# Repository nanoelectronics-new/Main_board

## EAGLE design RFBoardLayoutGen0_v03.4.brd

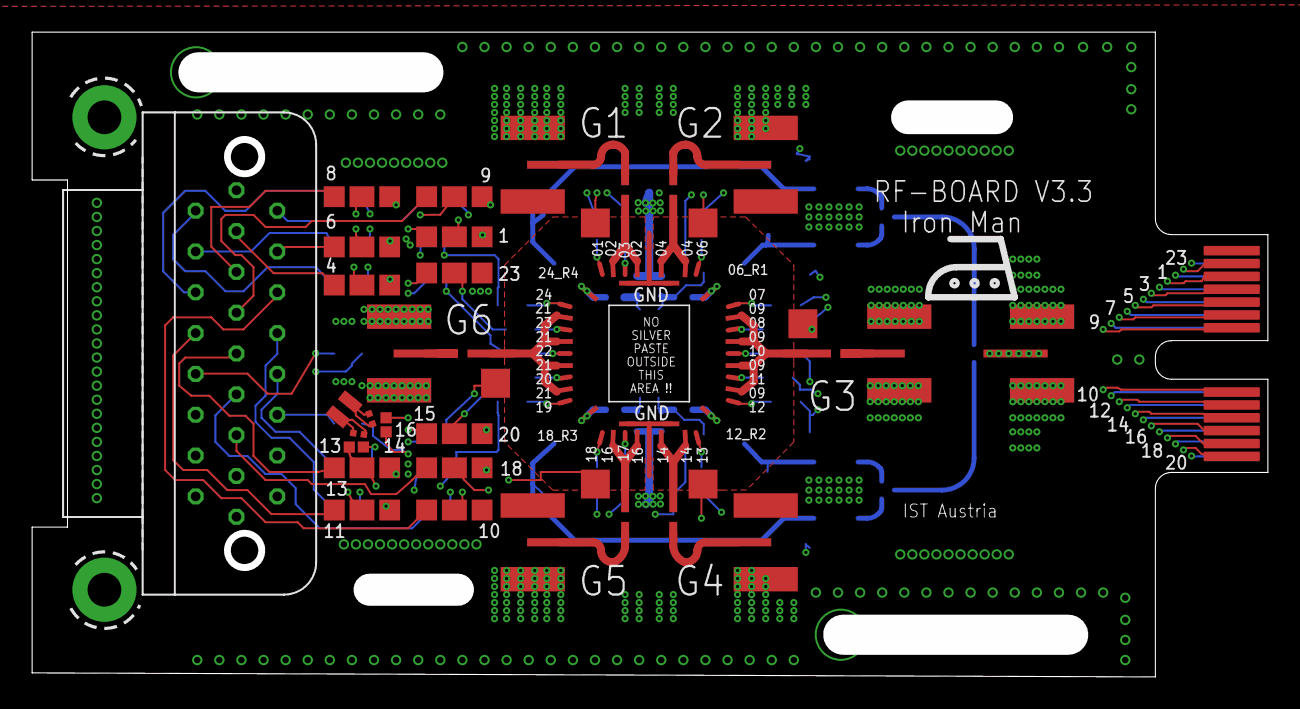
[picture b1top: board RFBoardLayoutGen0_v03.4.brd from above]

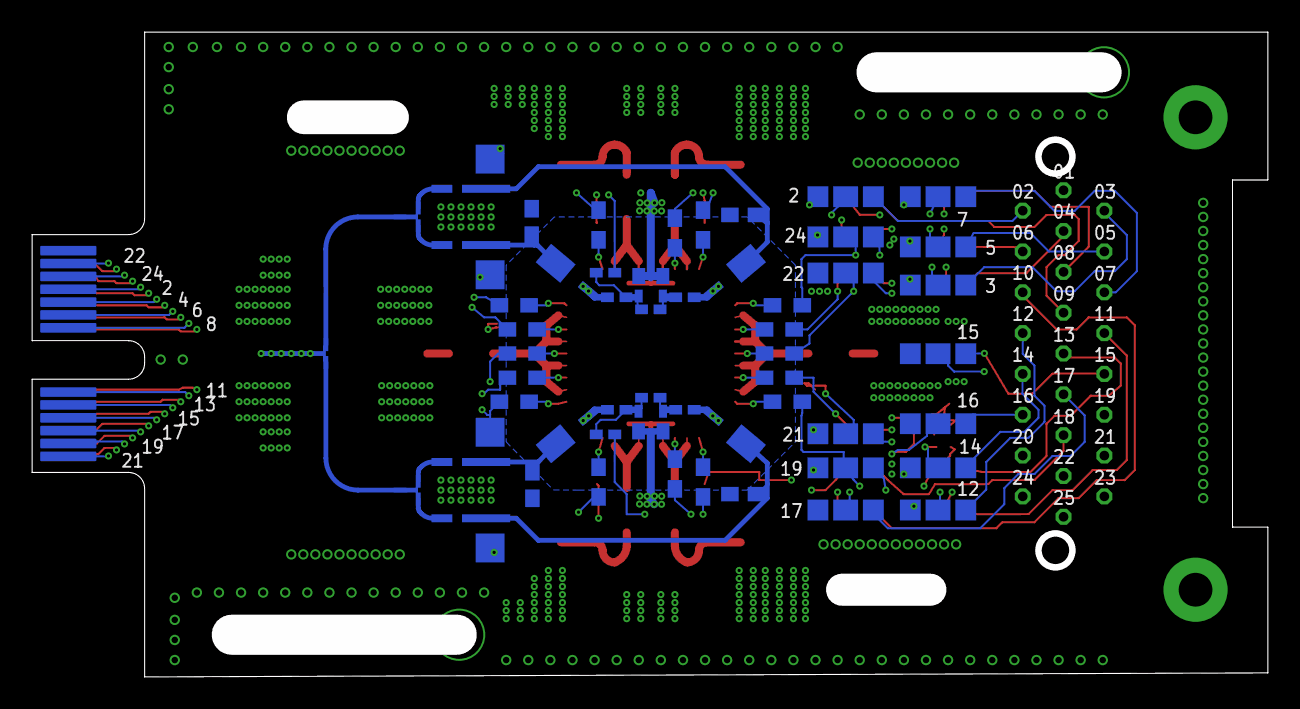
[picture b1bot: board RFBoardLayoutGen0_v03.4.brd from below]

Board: 6 copper layers, 76.9 x 40.1 mm, 88 parts (9 on the bottom side), 96 nets.

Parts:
B$1, B$3, B$4, B$6, B$8, B$10: BIASTEEDOWN; BIAS_TEE_DOWN_0603
B$2, B$5, B$7, B$9: BIASTEEUP; BIAS_TEE_UP_0603
E$2: 25_SOCKET_M83513/13-D_V2
L$1, L$2, L$3, L$4: L_MATCH
LP$1, LP$2, LP$3, LP$4, LP$5, LP$6, LP$15, LP$16, LP$17, LP$18, LP$19, LP$20: LP-FILTER/1-STAGETOP; LP-FILTER/1_STAGE/OS/0603_TOP
LP$7, LP$8, LP$9, LP$10, LP$11, LP$12, LP$13, LP$14, LP$21, LP$22, LP$23, LP$24: LP-FILTER/1-STAGEBOT; LP-FILTER/1_STAGE/OS/0603_BOTTOM
R$1, R$3, R$6, R$7, R$9, R$10, R$11, R$12, R$19, R$20, R$22, R$23, R$24, R$25, R$29, R$30: 10K; LP-FILTER/RESISTOR/0603_BOTTOM
S$1, S$2, S$3, S$4, S$5, S$6, S$7: MC-921WIDE; SMP_STRAIGHT_MINI_WIDE
TP1, TP2, TP3, TP4: TPTP07SQ; TP07SQ
U$1: MEC8-113-02-L-D-RA1MBRD; MEC8-113-02-L-D-RA1
U$2: TEMPSENS; RX-BR_V1
U$3, U$4, U$5: TJUNCTION; T_JUNCTION_0.3MM
U$6: 24DC+10RF_V2.0; 24DC+10RF/400MU-PADS/0.7X0.7_V2.0
U$7, U$8, U$9, U$10: LP-FILTER/CAPACITOR/0603; LP-FILTER/CAPACITOR/0603_BOTTOM
U$11, U$12, U$13, U$14: LP-FILTER/VARACTOR/0402
U$15, U$16, U$17, U$18: LP-FILTER/CAPACITOR/0402
U$19, U$20, U$21, U$22: LP-FILTER/RESISTOR/0402; LP-FILTER/CAPACITOR/0402

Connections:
C$1: E$2.01, LP$16.$1
C$2: E$2.02, LP$10.$1
C$3: E$2.03, LP$9.$1
C$4: E$2.04, LP$3.$1
C$5: E$2.05, LP$8.$1
C$6: E$2.06, LP$2.$1
C$7: E$2.07, LP$7.$1
C$8: E$2.08, LP$1.$1
C$9: E$2.09, LP$15.$1
C$10: E$2.10, LP$20.$1
C$11: E$2.11, LP$6.$1
C$12: E$2.12, LP$14.$1
C$13: E$2.13, LP$5.$1
C$14: E$2.14, LP$13.$1
C$15: E$2.15, LP$4.$1
C$16: E$2.16, LP$12.$1
C$17: E$2.17, LP$11.$1
C$18: E$2.18, LP$19.$1
C$19: E$2.19, LP$24.$1
C$20: E$2.20, LP$18.$1
C$21: E$2.21, LP$23.$1
C$22: E$2.22, LP$22.$1
C$23: E$2.23, LP$17.$1
C$24: E$2.24, LP$21.$1
D$1: LP$16.$4, R$1.IN, U$1.21
D$2: B$1.LF, LP$10.$4, U$1.20
D$3: LP$9.$4, R$3.IN, U$1.19
D$4: B$2.LF, LP$3.$4, U$1.18
D$5: LP$8.$4, U$1.17, U$22.IN
D$6: B$8.LF, LP$2.$4, R$6.IN, U$1.16
D$7: LP$7.$4, R$25.IN, U$1.15
D$8: LP$1.$4, R$7.IN, U$1.14
D$9: B$3.LF, LP$15.$4, U$1.13
D$10: LP$20.$4, R$9.IN, U$1.11
D$11: LP$6.$4, R$10.IN, U$1.12
D$12: B$9.LF, LP$14.$4, R$11.IN, U$1.9
D$13: LP$5.$4, R$12.IN, TP4.TP, U$1.10
D$14: B$4.LF, LP$13.$4, TP3.TP, U$1.7
D$15: LP$4.$4, TP1.TP, U$1.8, U$21.OUT
D$16: B$5.LF, LP$12.$4, TP2.TP, U$1.5
D$17: LP$11.$4, R$29.IN, U$1.6
D$18: B$10.LF, LP$19.$4, R$30.IN, U$1.3
D$19: LP$24.$4, R$19.IN, U$1.4
D$20: LP$18.$4, R$20.IN, U$1.1
D$21: B$6.LF, LP$23.$4, U$1.2
D$22: LP$22.$4, R$22.IN, U$1.24
D$23: LP$17.$4, R$23.IN, U$1.23
D$24: B$7.LF, LP$21.$4, R$24.IN, U$1.22
DC$1: R$1.OUT, U$6.DC$01
DC$3: R$3.OUT, U$6.DC§03
DC$5: B$2.OUT, U$6.RF$04_G21, U$6.RF$04_G22
DC$6: R$6.OUT, U$6.DC§06
DC$10: B$3.OUT, U$6.RF$09_G31, U$6.RF$09_G32, U$6.RF$09_G33, U$6.RF$09_G34
DC$13: R$12.OUT, U$6.DC$13
DC$19: R$19.OUT, U$6.DC§19
DC$20: R$20.OUT, U$6.DC§20
DC$24: R$24.OUT, U$6.DC§24
GND: E$2.25, LP$1.$6, LP$2.$6, LP$3.$6, LP$4.$6, LP$5.$6, LP$6.$6, LP$7.$6, LP$8.$6, LP$9.$6, LP$10.$6, LP$11.$6, LP$12.$6, LP$13.$6, LP$14.$6, LP$15.$6, LP$16.$6, LP$17.$6, LP$18.$6, LP$19.$6, LP$20.$6, LP$21.$6, LP$22.$6, LP$23.$6, LP$24.$6, S$1.2@1, S$1.2@2, S$2.2@1, S$2.2@2, S$3.2@1, S$3.2@2, S$4.2@1, S$4.2@2, S$5.2@1, S$5.2@2, S$6.2@1, S$6.2@2, S$7.2@1, S$7.2@2, U$1.25, U$1.26, U$6.GND$1, U$6.GND$2, U$6.GND$3, U$6.GND$4, U$6.GND$5, U$6.GND$6, U$7.OUT, U$8.OUT, U$9.OUT, U$10.OUT, U$11.OUT, U$12.OUT, U$13.OUT, U$14.OUT
unnamed: B$6.HF, S$1.1
unnamed: L$3.OUT, U$6.RF$12_R2, U$18.IN
unnamed: B$1.OUT, U$6.RF$02_G11, U$6.RF$02_G12
unnamed: R$25.OUT, U$6.DC§07
unnamed: B$1.HF, S$7.1
unnamed: B$2.HF, S$6.1
unnamed: B$4.OUT, U$6.RF$14_G41, U$6.RF$14_G42
unnamed: B$5.OUT, U$6.RF$16_G51, U$6.RF$16_G52
unnamed: L$4.OUT, U$6.RF$18_R3, U$16.IN
unnamed: L$1.OUT, U$6.RF$24_R4, U$15.OUT
unnamed: L$2.OUT, U$6.RF$06_R1, U$17.OUT
unnamed: R$7.OUT, U$6.DC§08
unnamed: B$9.OUT, L$3.IN, U$9.IN
unnamed: B$8.OUT, L$2.IN, U$10.IN
unnamed: B$9.HF, U$5.P$3
unnamed: B$5.HF, S$2.1
unnamed: B$4.HF, S$3.1
unnamed: B$3.HF, S$4.1
unnamed: B$7.HF, U$3.P$3
unnamed: B$6.OUT, U$6.RF$21_G61, U$6.RF$21_G62, U$6.RF$21_G63, U$6.RF$21_G64
unnamed: S$5.1, U$4.P$1
unnamed: B$10.HF, U$5.P$2
unnamed: B$8.HF, U$3.P$2
unnamed: R$9.OUT, U$6.DC§10
unnamed: U$3.P$1, U$4.P$3
unnamed: U$4.P$2, U$5.P$1
unnamed: R$10.OUT, U$6.DC§11
unnamed: R$11.OUT, U$6.DC§12
unnamed: U$13.IN, U$17.IN, U$19.OUT, U$22.OUT
unnamed: R$29.OUT, U$6.DC§17
unnamed: R$30.OUT, U$6.DC§18
unnamed: R$22.OUT, U$6.DC§22
unnamed: R$23.OUT, U$6.DC§23
unnamed: U$12.IN, U$18.OUT, U$20.OUT, U$21.IN
unnamed: U$14.IN, U$15.IN, U$19.IN
unnamed: U$11.IN, U$16.OUT, U$20.IN
RF$3: B$10.OUT, L$4.IN, U$8.IN
RF$4: B$7.OUT, L$1.IN, U$7.IN

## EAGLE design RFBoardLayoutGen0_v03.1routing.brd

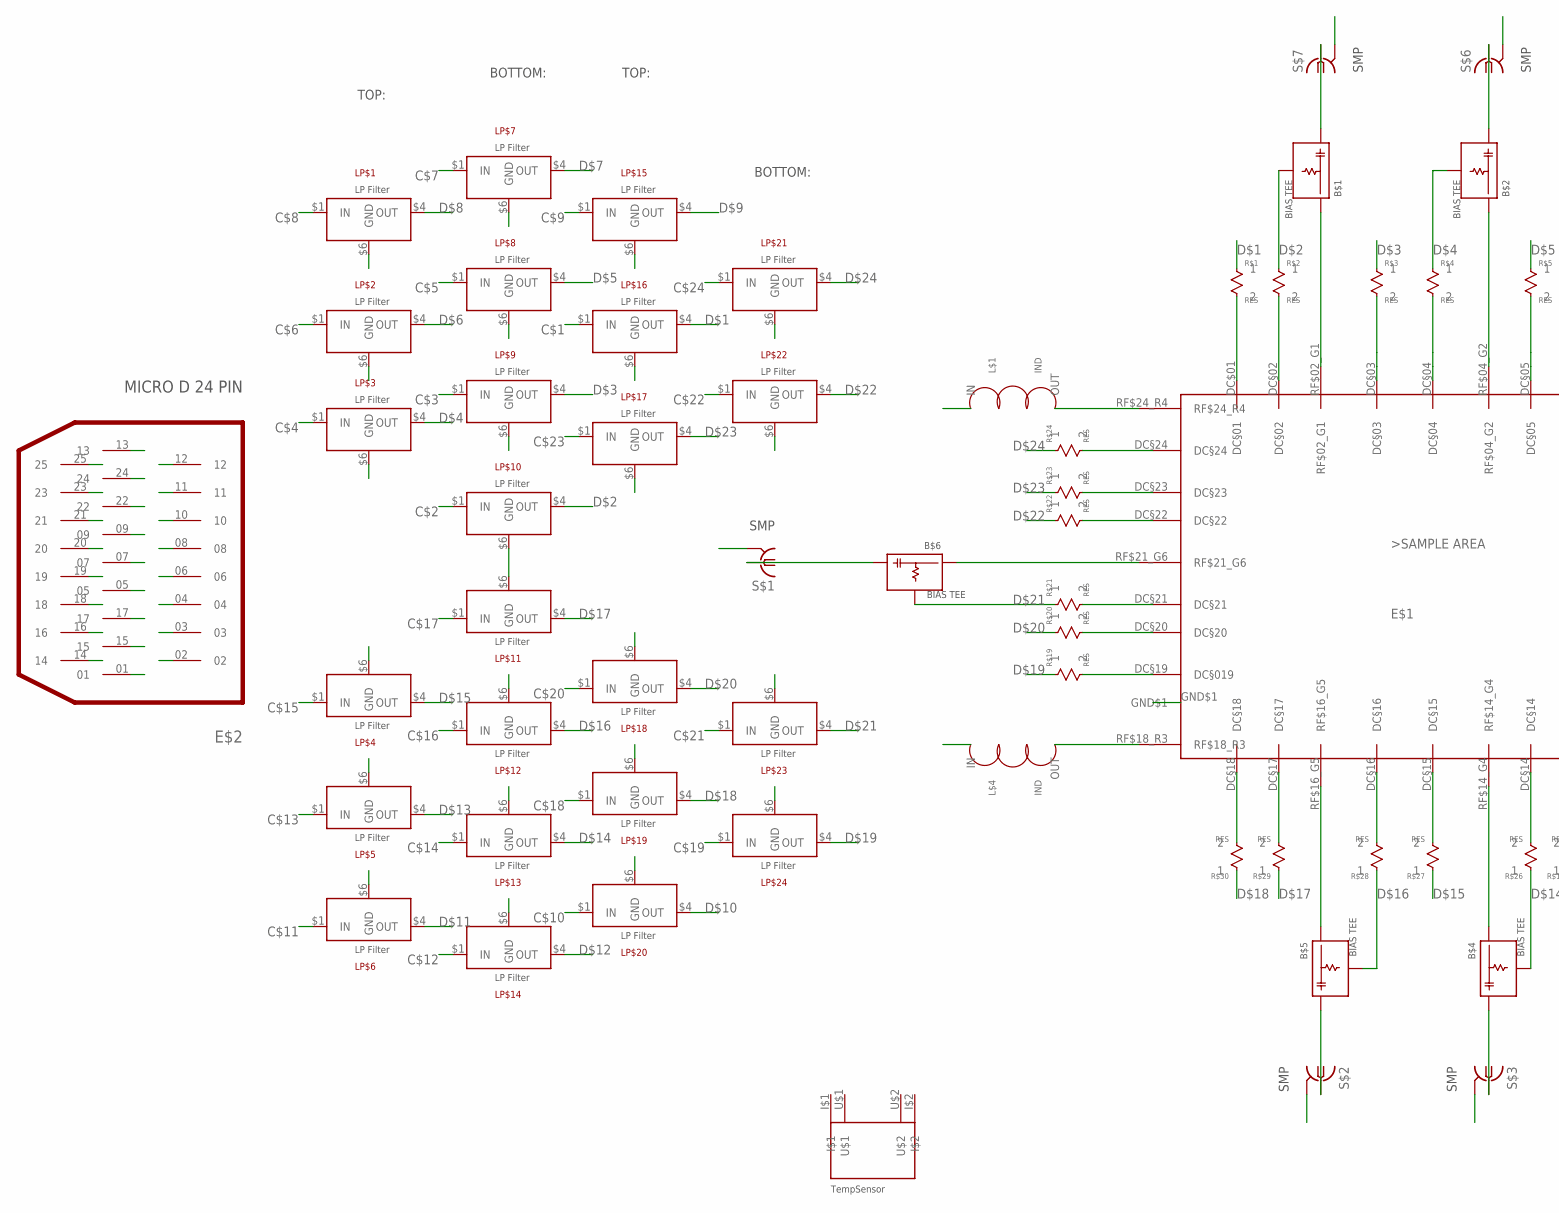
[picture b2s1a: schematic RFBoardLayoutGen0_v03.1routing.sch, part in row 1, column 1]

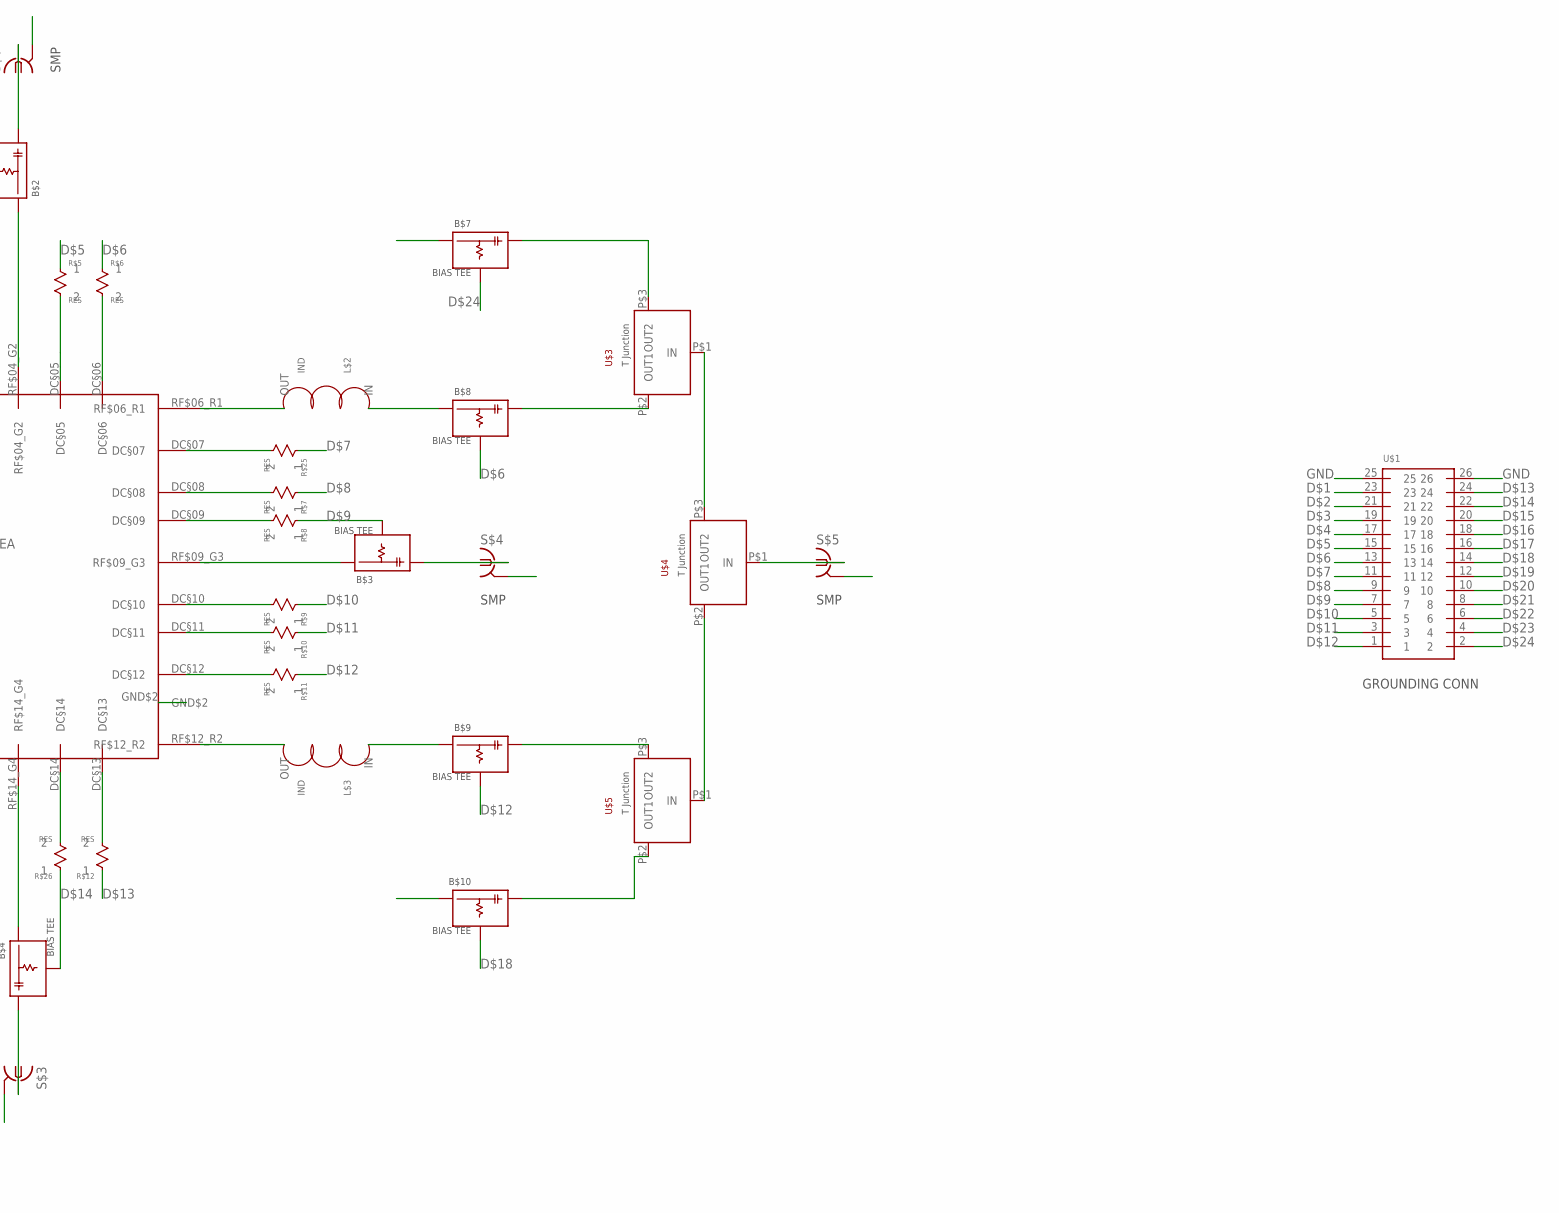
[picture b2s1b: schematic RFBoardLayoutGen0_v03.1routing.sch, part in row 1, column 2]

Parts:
B$1, B$3, B$4, B$6, B$8, B$10: BIASTEEDOWN; BIAS_TEE_DOWN_0603
B$2, B$5, B$7, B$9: BIASTEEUP; BIAS_TEE_UP_0603
E$1: 24DC+10RF; 24DC+10RF/400MU-PADS/0.7X0.7_V1.0
E$2: 25_SOCKET_M83513(13-DPINOUT2; 25_SOCKET_M83513/13-D_V2
L$1, L$2, L$3, L$4: L_MATCH
LP$1, LP$2, LP$3, LP$4, LP$5, LP$6, LP$15, LP$16, LP$17, LP$18, LP$19, LP$20: LP-FILTER/1-STAGETOP; LP-FILTER/1_STAGE/OS/0603_TOP
LP$7, LP$8, LP$9, LP$10, LP$11, LP$12, LP$13, LP$14, LP$21, LP$22, LP$23, LP$24: LP-FILTER/1-STAGEBOT; LP-FILTER/1_STAGE/OS/0603_BOTTOM
R$1, R$2, R$3, R$4, R$5, R$6, R$7, R$8, R$9, R$10, R$11, R$12, R$19, R$20, R$21, R$22, R$23, R$24, R$25, R$26, R$27, R$28, R$29, R$30: 10K; LP-FILTER/RESISTOR/0603_BOTTOM
S$1, S$2, S$3, S$4, S$5, S$6, S$7: MC-921; SMP_STRAIGHT_MINI
U$1: MEC8-113-02-L-D-RA1MBRD; MEC8-113-02-L-D-RA1
U$2: TEMPSENS; RX-BR_V1
U$3, U$4, U$5: TJUNCTION; T_JUNCTION_0.3MM

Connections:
C$1: E$2.01, LP$16.$1 (IN)
C$2: E$2.02, LP$10.$1 (IN)
C$3: E$2.03, LP$9.$1 (IN)
C$4: E$2.04, LP$3.$1 (IN)
C$5: E$2.05, LP$8.$1 (IN)
C$6: E$2.06, LP$2.$1 (IN)
C$7: E$2.07, LP$7.$1 (IN)
C$8: E$2.08, LP$1.$1 (IN)
C$9: E$2.09, LP$15.$1 (IN)
C$10: E$2.10, LP$20.$1 (IN)
C$11: E$2.11, LP$6.$1 (IN)
C$12: E$2.12, LP$14.$1 (IN)
C$13: E$2.13, LP$5.$1 (IN)
C$14: E$2.14, LP$13.$1 (IN)
C$15: E$2.15, LP$4.$1 (IN)
C$16: E$2.16, LP$12.$1 (IN)
C$17: E$2.17, LP$11.$1 (IN)
C$18: E$2.18, LP$19.$1 (IN)
C$19: E$2.19, LP$24.$1 (IN)
C$20: E$2.20, LP$18.$1 (IN)
C$21: E$2.21, LP$23.$1 (IN)
C$22: E$2.22, LP$22.$1 (IN)
C$23: E$2.23, LP$17.$1 (IN)
C$24: E$2.24, LP$21.$1 (IN)
D$1: LP$16.$4 (OUT), R$1.IN (1), U$1.23
D$2: B$1.LF, LP$10.$4 (OUT), R$2.IN (1), U$1.21
D$3: LP$9.$4 (OUT), R$3.IN (1), U$1.19
D$4: B$2.LF, LP$3.$4 (OUT), R$4.IN (1), U$1.17
D$5: LP$8.$4 (OUT), R$5.IN (1), U$1.15
D$6: B$8.LF, LP$2.$4 (OUT), R$6.IN (1), U$1.13
D$7: LP$7.$4 (OUT), R$25.IN (1), U$1.11
D$8: LP$1.$4 (OUT), R$7.IN (1), U$1.9
D$9: B$3.LF, LP$15.$4 (OUT), R$8.IN (1), U$1.7
D$10: LP$20.$4 (OUT), R$9.IN (1), U$1.5
D$11: LP$6.$4 (OUT), R$10.IN (1), U$1.3
D$12: B$9.LF, LP$14.$4 (OUT), R$11.IN (1), U$1.1
D$13: LP$5.$4 (OUT), R$12.IN (1), U$1.24
D$14: B$4.LF, LP$13.$4 (OUT), R$26.IN (1), U$1.22
D$15: LP$4.$4 (OUT), R$27.IN (1), U$1.20
D$16: B$5.LF, LP$12.$4 (OUT), R$28.IN (1), U$1.18
D$17: LP$11.$4 (OUT), R$29.IN (1), U$1.16
D$18: B$10.LF, LP$19.$4 (OUT), R$30.IN (1), U$1.14
D$19: LP$24.$4 (OUT), R$19.IN (1), U$1.12
D$20: LP$18.$4 (OUT), R$20.IN (1), U$1.10
D$21: B$6.LF, LP$23.$4 (OUT), R$21.IN (1), U$1.8
D$22: LP$22.$4 (OUT), R$22.IN (1), U$1.6
D$23: LP$17.$4 (OUT), R$23.IN (1), U$1.4
D$24: B$7.LF, LP$21.$4 (OUT), R$24.IN (1), U$1.2
DC$1: E$1.DC$01 (DC§01), R$1.OUT (2)
DC$2: E$1.DC§02, R$2.OUT (2)
DC$3: E$1.DC§03, R$3.OUT (2)
DC$4: E$1.DC§04, R$4.OUT (2)
DC$5: E$1.DC§05, R$5.OUT (2)
DC$6: E$1.DC§06, R$6.OUT (2)
DC$7: E$1.DC§07, R$25.OUT (2)
DC$8: E$1.DC§08, R$7.OUT (2)
DC$9: E$1.DC§09, R$8.OUT (2)
DC$10: E$1.DC§10, R$9.OUT (2)
DC$11: E$1.DC§11, R$10.OUT (2)
DC$12: E$1.DC§12, R$11.OUT (2)
DC$13: E$1.DC§13, R$12.OUT (2)
DC$14: E$1.DC§14, R$26.OUT (2)
DC$15: E$1.DC§15, R$27.OUT (2)
DC$16: E$1.DC§16, R$28.OUT (2)
DC$17: E$1.DC§17, R$29.OUT (2)
DC$18: E$1.DC§18, R$30.OUT (2)
DC$19: E$1.DC§19 (DC§019), R$19.OUT (2)
DC$20: E$1.DC§20, R$20.OUT (2)
DC$21: E$1.DC§21, R$21.OUT (2)
DC$22: E$1.DC§22, R$22.OUT (2)
DC$23: E$1.DC§23, R$23.OUT (2)
DC$24: E$1.DC§24, R$24.OUT (2)
GND: E$1.GND$1, E$1.GND$2, E$2.25, LP$1.$6 (GND), LP$2.$6 (GND), LP$3.$6 (GND), LP$4.$6 (GND), LP$5.$6 (GND), LP$6.$6 (GND), LP$7.$6 (GND), LP$8.$6 (GND), LP$9.$6 (GND), LP$10.$6 (GND), LP$11.$6 (GND), LP$12.$6 (GND), LP$13.$6 (GND), LP$14.$6 (GND), LP$15.$6 (GND), LP$16.$6 (GND), LP$17.$6 (GND), LP$18.$6 (GND), LP$19.$6 (GND), LP$20.$6 (GND), LP$21.$6 (GND), LP$22.$6 (GND), LP$23.$6 (GND), LP$24.$6 (GND), S$1.2@1 (GND), S$1.2@2 (GND), S$2.2@1 (GND), S$2.2@2 (GND), S$3.2@1 (GND), S$3.2@2 (GND), S$4.2@1 (GND), S$4.2@2 (GND), S$5.2@1 (GND), S$5.2@2 (GND), S$6.2@1 (GND), S$6.2@2 (GND), S$7.2@1 (GND), S$7.2@2 (GND), U$1.25, U$1.26
unnamed: B$6.HF, S$1.1
unnamed: E$1.RF$12_R2, L$3.OUT
unnamed: B$1.OUT, E$1.RF$02_G1
unnamed: B$2.OUT, E$1.RF$04_G2
unnamed: B$1.HF, S$7.1
unnamed: B$2.HF, S$6.1
unnamed: B$5.OUT, E$1.RF$16_G5
unnamed: B$4.OUT, E$1.RF$14_G4
unnamed: E$1.RF$18_R3, L$4.OUT
unnamed: E$1.RF$24_R4, L$1.OUT
unnamed: E$1.RF$06_R1, L$2.OUT
unnamed: B$3.OUT, E$1.RF$09_G3
unnamed: B$9.OUT, L$3.IN
unnamed: B$8.OUT, L$2.IN
unnamed: B$9.HF, U$5.P$3 (OUT2)
unnamed: B$5.HF, S$2.1
unnamed: B$4.HF, S$3.1
unnamed: B$3.HF, S$4.1
unnamed: B$7.HF, U$3.P$3 (OUT2)
unnamed: B$6.OUT, E$1.RF$21_G6
unnamed: S$5.1, U$4.P$1 (IN)
unnamed: B$10.HF, U$5.P$2 (OUT1)
unnamed: B$8.HF, U$3.P$2 (OUT1)
unnamed: U$3.P$1 (IN), U$4.P$3 (OUT2)
unnamed: U$4.P$2 (OUT1), U$5.P$1 (IN)
RF$3: B$10.OUT, L$4.IN
RF$4: B$7.OUT, L$1.IN

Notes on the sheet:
TOP:
BOTTOM:

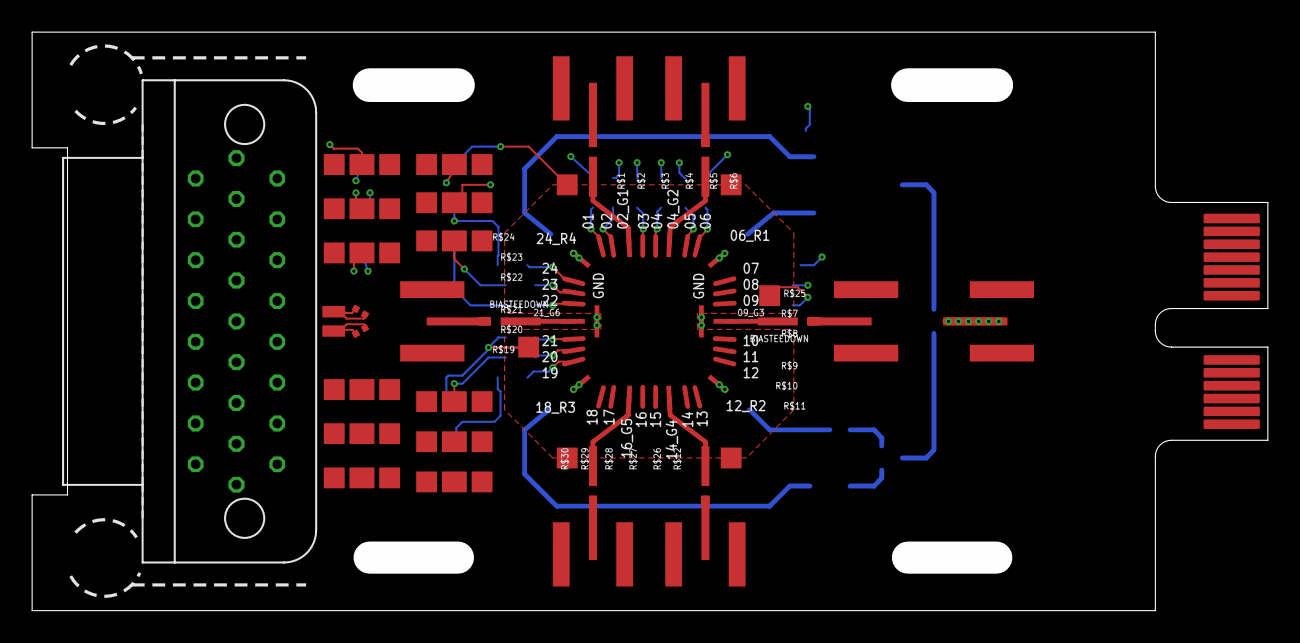
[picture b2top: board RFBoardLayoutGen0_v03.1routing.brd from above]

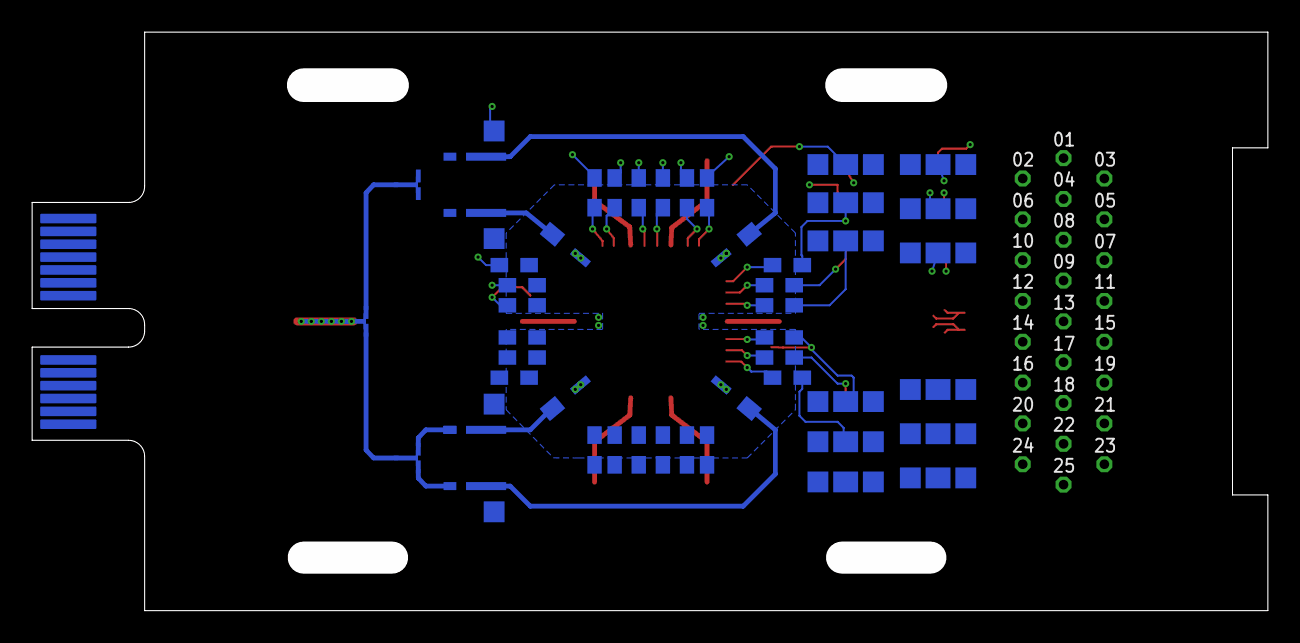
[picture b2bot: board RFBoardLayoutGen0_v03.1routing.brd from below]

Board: 6 copper layers, 76.9 x 36.0 mm, 77 parts (9 on the bottom side), 100 nets.

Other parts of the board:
E$30: SMD0.8-0,5

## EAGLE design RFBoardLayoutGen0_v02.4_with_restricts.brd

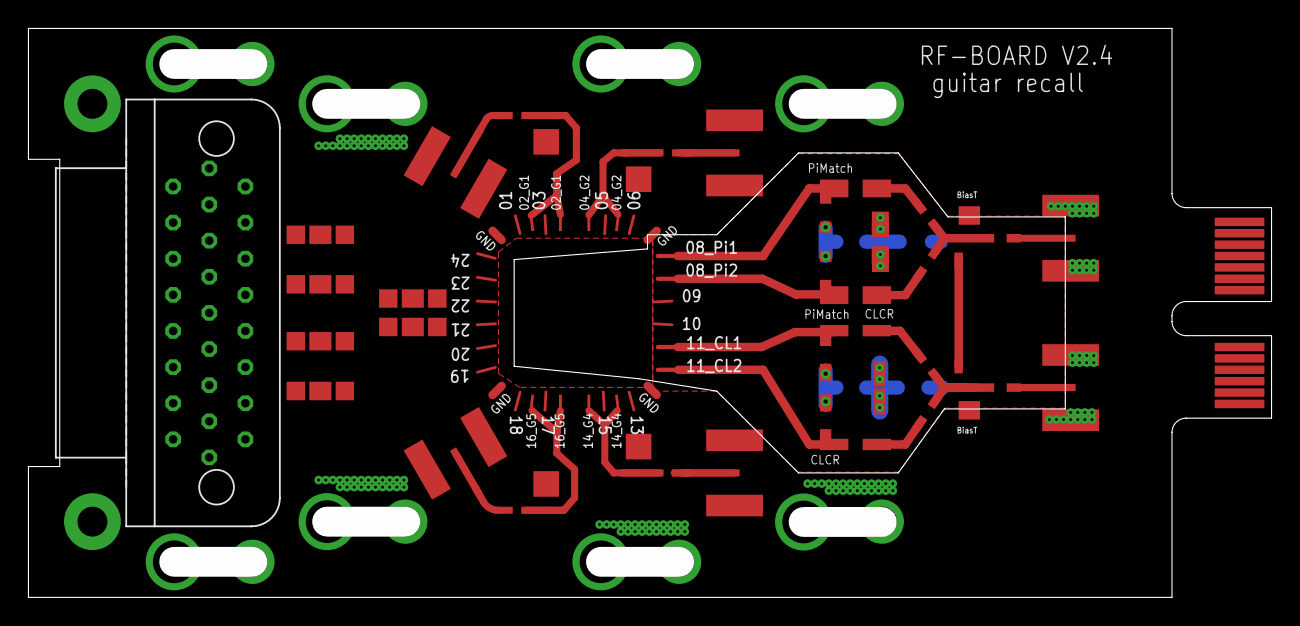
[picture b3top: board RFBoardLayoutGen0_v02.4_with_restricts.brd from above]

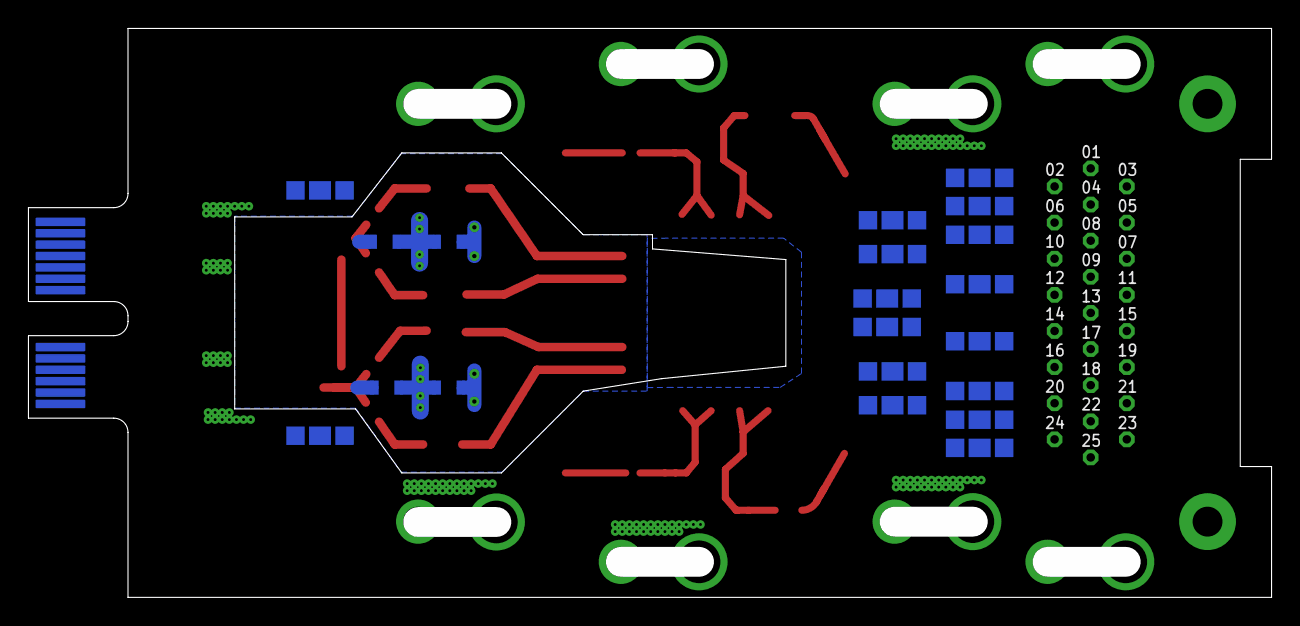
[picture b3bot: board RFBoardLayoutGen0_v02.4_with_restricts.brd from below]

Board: 4 copper layers, 87.4 x 40.0 mm, 61 parts (14 on the bottom side), 45 nets.

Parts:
B$1, B$4: BIAS_TEE_DOWN_0603
B$2, B$5: BIAS_TEE_UP_0603
E$1: 24DC+4RF/400MU-PADS/10.0X10.0_V1.5
E$2: 25_SOCKET_M83513/13-D
E$3: MEC8-113-02-L-D-RA1
E$4, E$5, E$6, E$7, E$8, E$11, E$12, E$13, E$14, E$15: LP-FILTER/1_STAGE/OS/0603_TOP_V1_01
E$9: PI_MATCH_V01_UP
E$10: CLCR_V01_DOWN
E$16, E$17, E$18, E$19, E$20, E$21, E$22, E$23, E$24, E$25, E$27, E$28: LP-FILTER/1_STAGE/OS/0603_BOTTOM_V1_01
E$26, E$33: SMP_STRAIGHT_MINI_WIDE_V1_01
E$29: BIAS_TEE_UP_V01
E$30: BIAS_TEE_DOWN_V01
E$31, E$34, E$35, E$36, E$38, E$39, E$40, E$41, E$42, E$43, E$44, E$45, E$46, E$47, E$48, E$49, E$50, E$51, E$52, E$54: SMD1-0,6
E$32: PI_MATCH_V01_DOWN
E$37: CLCR_V01_UP
S$2, S$3, S$6, S$7: MC-921SMALL; SMP_STRAIGHT_MINI_WIDE

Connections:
D$2: B$1.LF, E$3.19, E$6.$2
D$4: B$2.LF, E$3.21, E$4.$2
GND: E$1.P$1, E$1.P$3, E$1.P$6, E$2.13, E$3.14, E$4.GND@1, E$5.GND@1, E$6.GND@1, E$7.GND@1, E$8.GND@1, E$11.GND@1, E$12.GND@1, E$13.GND@1, E$14.GND@1, E$15.GND@1, E$16.GND@1, E$17.GND@1, E$18.GND@1, E$19.GND@1, E$20.GND@1, E$21.GND@1, E$22.GND@1, E$23.GND@1, E$24.GND@1, E$25.GND@1, E$26.GND, E$26.GND@1, E$27.GND@1, E$28.GND@1, E$33.GND, E$33.GND@1, S$2.2@1, S$2.2@2, S$3.2@1, S$3.2@2, S$6.2@1, S$6.2@2, S$7.2@1, S$7.2@2
S$1: E$1.P$30, E$22.$2
S$2: E$1.P$44, E$3.8, E$21.$2, E$47.1
S$55: E$1.P$49, E$3.2, E$27.$2, E$46.1
S$67: E$2.24, E$11.$1
S$68: E$1.P$29, E$3.9, E$15.$2
S$76: E$2.11, E$15.$1
S$79: E$1.P$27, E$3.16, E$19.$2
S$80: E$2.12, E$19.$1
S$83: E$2.23, E$22.$1
S$84: E$1.P$26, E$3.17, E$8.$2
S$85: E$2.25, E$8.$1
S$86: E$1.P$38, E$3.18, E$16.$2, E$36.1
S$88: E$2.01, E$16.$1
S$89: E$1.P$31, E$3.7, E$7.$2
S$90: E$2.10, E$7.$1
S$95: E$2.22, E$21.$1
S$144: E$2.14, E$6.$1
S$145: E$1.P$40, E$3.20, E$23.$2
S$146: E$2.02, E$23.$1
S$147: B$5.LF, E$3.6, E$17.$2
S$149: E$2.15, E$4.$1
S$150: E$1.P$42, E$3.24, E$20.$2
S$151: E$2.03, E$20.$1
S$152: E$1.P$45, E$3.5, E$12.$2
S$154: E$2.09, E$12.$1
S$155: B$4.LF, E$3.4, E$18.$2
S$156: E$2.21, E$17.$1
S$157: E$1.P$4, E$3.3, E$5.$2
S$158: E$2.08, E$5.$1
S$160: E$2.20, E$18.$1
S$162: E$2.16, E$24.$1
S$168: E$2.17, E$14.$1
S$169: E$1.P$34, E$3.26, E$25.$2
S$170: E$2.05, E$25.$1
S$171: E$2.07, E$27.$1
S$174: E$1.P$28, E$3.15, E$11.$2
S$175: E$2.06, E$13.$1
S$177: E$1.P$35, E$3.11, E$28.$2
S$178: E$2.18, E$28.$1
S$183: E$3.12, E$13.$2, E$29.P$1
S$190: E$3.23, E$14.$2, E$30.P$1
S$211: E$1.P$43, E$3.22, E$24.$2, E$34.1

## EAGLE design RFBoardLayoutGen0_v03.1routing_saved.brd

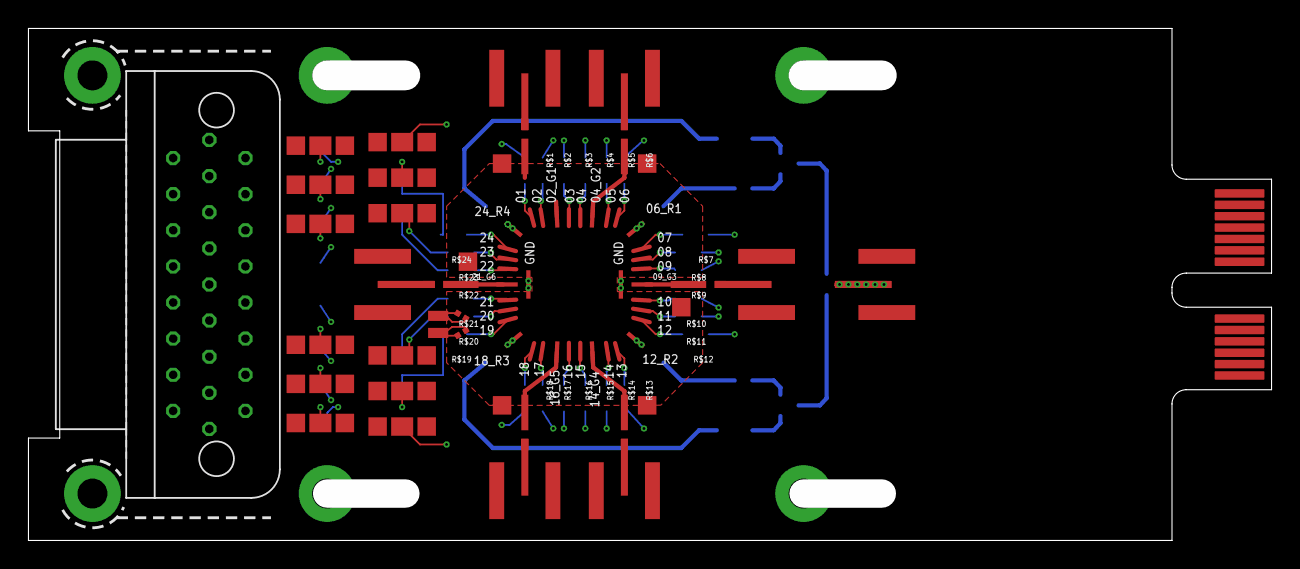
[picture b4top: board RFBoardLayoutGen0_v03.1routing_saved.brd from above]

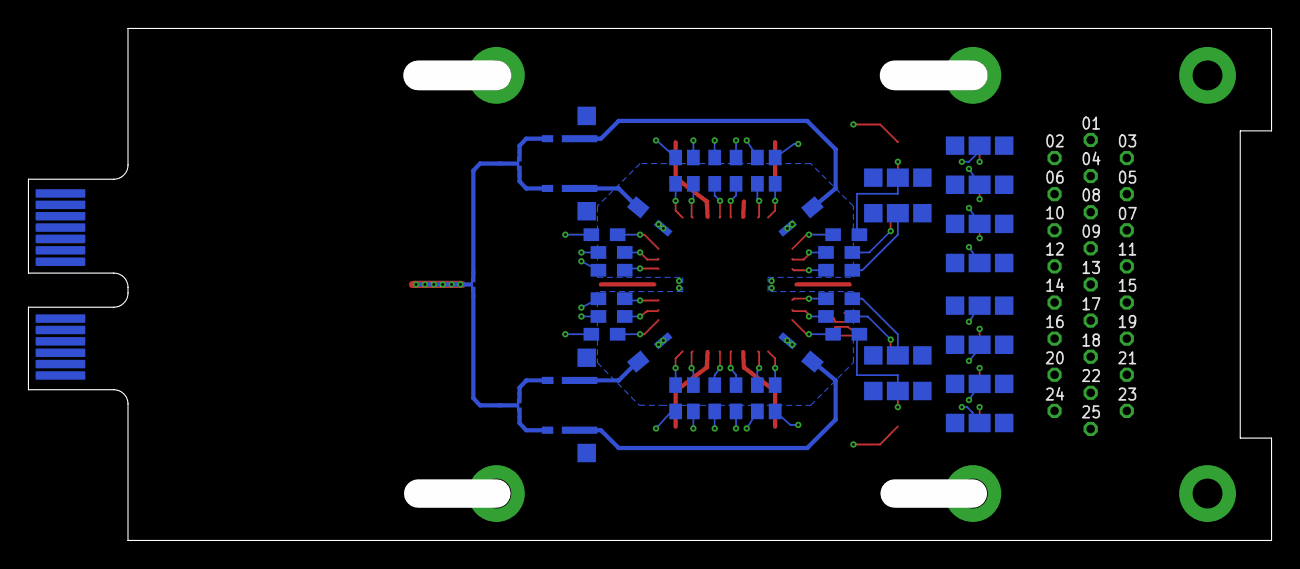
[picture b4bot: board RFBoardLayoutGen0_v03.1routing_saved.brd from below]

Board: 6 copper layers, 87.4 x 36.0 mm, 77 parts (9 on the bottom side), 48 nets.

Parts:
B$1, B$4, B$8, B$10: BIAS_TEE_DOWN_0603
B$2, B$3, B$5, B$6, B$7, B$9: BIAS_TEE_UP_0603
E$1: 24DC+10RF/400MU-PADS/0.7X0.7_V1.0
E$2: 25_SOCKET_M83513/13-D
E$3: MEC8-113-02-L-D-RA1
E$30: SMD0.8-0,5
E$40: RX-BR_V1
E$48, E$50, E$51: T_JUNCTION_0.3MM
L$1, L$2, L$3, L$4: L_MATCH
LP$1, LP$2, LP$3, LP$4, LP$5, LP$6, LP$15, LP$16, LP$17, LP$18, LP$19, LP$20: LP-FILTER/1_STAGE/OS/0603_TOP
LP$7, LP$8, LP$9, LP$10, LP$11, LP$12, LP$13, LP$14, LP$21, LP$22, LP$23, LP$24: LP-FILTER/1_STAGE/OS/0603_BOTTOM
R$1, R$2, R$3, R$4, R$5, R$6, R$7, R$8, R$9, R$10, R$11, R$12, R$13, R$14, R$15, R$16, R$17, R$18, R$19, R$20, R$21, R$22, R$23, R$24: 10K; LP-FILTER/RESISTOR/0603_BOTTOM
S$1, S$2, S$3, S$4, S$5, S$6, S$7: SMP_STRAIGHT_MINI

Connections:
S$166: E$1.DC§24, R$24.IN
S$180: E$1.DC§23, R$23.IN
S$181: E$1.DC§22, R$22.IN
S$184: E$1.DC§21, R$21.IN
S$185: E$1.DC§20, R$20.IN
S$186: E$1.DC§19, R$19.IN
S$187: E$1.DC$01, R$1.OUT
S$188: E$1.DC§02, R$2.OUT
S$189: E$1.DC§03, R$3.OUT
S$191: E$1.DC§04, R$4.OUT
S$193: E$1.DC§05, R$5.OUT
S$194: E$1.DC§06, R$6.OUT
S$195: E$1.DC§07, R$7.OUT
S$196: E$1.DC§08, R$8.OUT
S$199: E$1.DC§09, R$9.OUT
S$201: E$1.DC§10, R$10.OUT
S$202: E$1.DC§11, R$11.OUT
S$203: E$1.DC§12, R$12.OUT
S$204: E$1.DC§13, R$13.IN
S$205: E$1.DC§14, R$14.IN
S$206: E$1.DC§17, R$17.IN
S$207: E$1.DC§16, R$16.IN
S$208: E$1.DC§15, R$15.IN
S$209: E$1.DC§18, R$18.IN
S$216: LP$22.$4, R$22.OUT
S$217: LP$17.$4, R$23.OUT
S$218: LP$21.$4, R$24.OUT
S$219: LP$23.$4, R$21.OUT
S$220: LP$18.$4, R$20.OUT
S$221: LP$24.$4, R$19.OUT
S$222: LP$16.$4, R$1.IN
S$223: LP$19.$4, R$18.OUT
S$224: LP$11.$4, R$17.OUT
S$225: LP$10.$4, R$2.IN
S$226: LP$12.$4, R$16.OUT
S$227: LP$4.$4, R$15.OUT
S$228: LP$13.$4, R$14.OUT
S$229: LP$5.$4, R$13.OUT
S$230: LP$9.$4, R$3.IN
S$231: LP$3.$4, R$4.IN
S$232: LP$8.$4, R$5.IN
S$233: LP$2.$4, R$6.IN
S$234: LP$7.$4, R$7.IN
S$235: LP$1.$4, R$8.IN
S$236: LP$14.$4, R$12.IN
S$237: LP$6.$4, R$11.IN
S$238: LP$15.$4, R$9.IN
S$239: LP$20.$4, R$10.IN

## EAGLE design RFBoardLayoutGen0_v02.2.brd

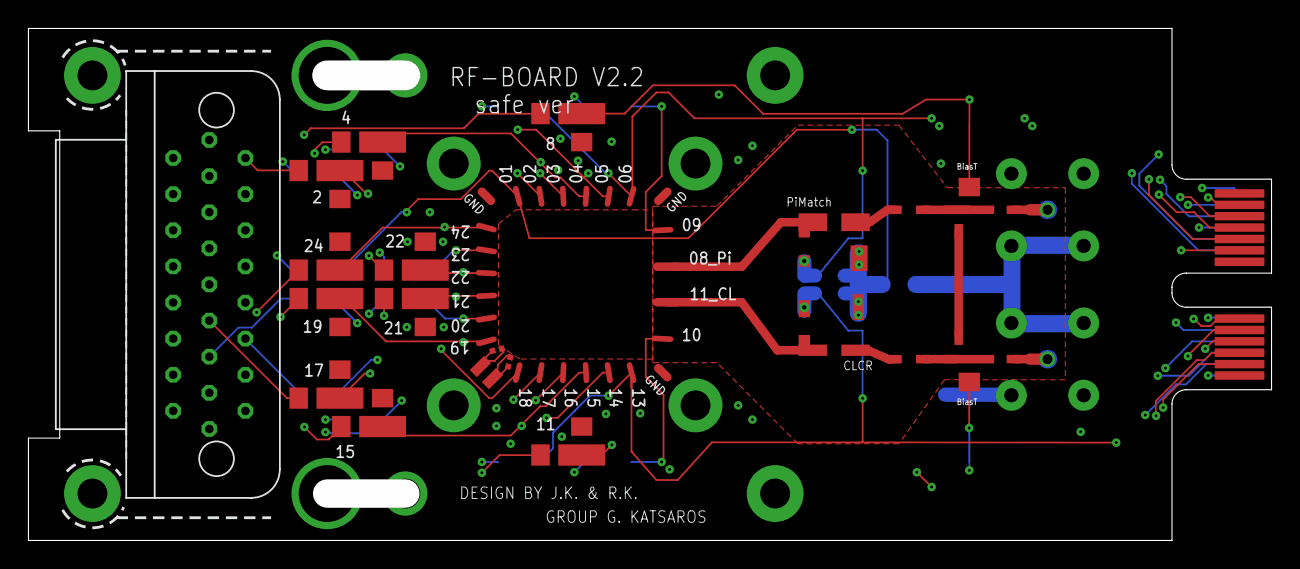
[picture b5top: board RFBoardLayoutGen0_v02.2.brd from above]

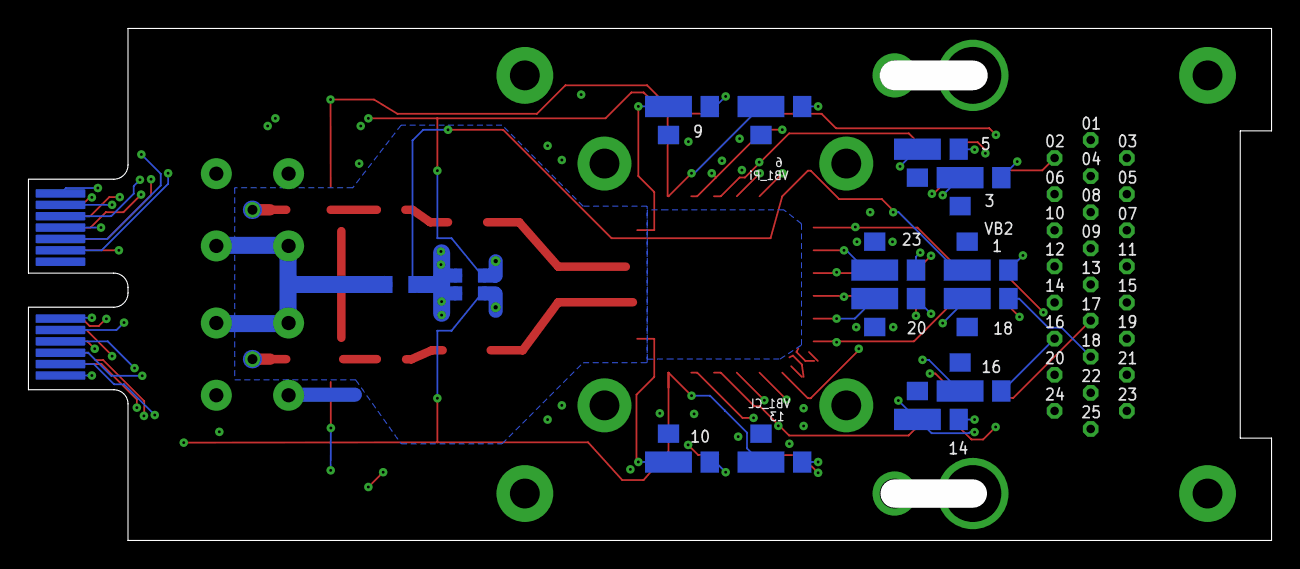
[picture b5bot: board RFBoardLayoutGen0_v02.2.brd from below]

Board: 4 copper layers, 87.4 x 36.0 mm, 46 parts (6 on the bottom side), 45 nets.

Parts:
E$1: 24DC+4RF/400MU-PADS/10.0X10.0_V1.3
E$2: 25_SOCKET_M83513/13-D
E$3: MEC8-113-02-L-D-RA1
E$4, E$6, E$7, E$14, E$15: LP-FILTER/1_STAGE/OS/V1_01
E$5, E$8, E$11, E$12, E$13: LP-FILTER/1_STAGE/OS/V1_02
E$9, E$10: SMD1.2-0,6
E$16, E$17, E$18, E$19, E$27, E$28: LP-FILTER/1_STAGE/OS/V1_03
E$20, E$21, E$22, E$23, E$24, E$25: LP-FILTER/1_STAGE/OS/V1_04
E$26, E$33: SMP_STRAIGHT_V02
E$29: BIAS_TEE_UP_V01
E$30: BIAS_TEE_DOWN_V01
E$31, E$34, E$35, E$36, E$38, E$39, E$41, E$42, E$44, E$45, E$46, E$47: SMD1-0,6
E$32: PI_MATCH_V01_DOWN
E$37: CLCR_V01_UP
E$40: RX-BR_V1

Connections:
GND1: E$1.P$1, E$1.P$3, E$1.P$6, E$2.13, E$3.163, E$4.GND@1, E$5.GND@3, E$6.GND@1, E$7.GND@1, E$8.GND@3, E$11.GND@3, E$12.GND@3, E$13.GND@3, E$14.GND@1, E$15.GND@1, E$16.GND@3, E$17.GND@3, E$18.GND@3, E$19.GND@3, E$20.GND@1, E$21.GND@1, E$22.GND@1, E$23.GND@1, E$24.GND@1, E$25.GND@1, E$26.P$3, E$26.P$4, E$26.P$5, E$27.GND@3, E$28.GND@3, E$33.P$4, E$33.P$5, E$33.P$6
S$55: E$1.P$49, E$3.173, E$27.$4, E$46.1
S$67: E$2.24, E$11.$6
S$68: E$1.P$29, E$3.137, E$15.$2
S$76: E$2.11, E$15.$1
S$79: E$1.P$27, E$3.162, E$19.$4
S$80: E$2.12, E$19.$6
S$81: E$1.P$30, E$3.169, E$22.$2
S$83: E$2.23, E$22.$1
S$84: E$1.P$26, E$3.133, E$8.$4
S$85: E$2.25, E$8.$6
S$86: E$1.P$38, E$3.161, E$9.1, E$16.$4
S$88: E$2.01, E$16.$6
S$89: E$1.P$31, E$3.138, E$7.$2
S$90: E$2.10, E$7.$1
S$91: E$1.P$44, E$3.170, E$21.$2
S$95: E$2.22, E$21.$1
S$116: E$1.P$39, E$3.132, E$6.$2
S$144: E$2.14, E$6.$1
S$145: E$1.P$40, E$3.160, E$23.$2
S$146: E$2.02, E$23.$1
S$147: E$1.P$2, E$3.131, E$4.$2
S$149: E$2.15, E$4.$1
S$150: E$1.P$42, E$3.158, E$20.$2
S$151: E$2.03, E$20.$1
S$152: E$1.P$45, E$3.139, E$12.$4
S$154: E$2.09, E$12.$6
S$155: E$1.P$46, E$3.171, E$17.$4
S$156: E$2.21, E$17.$6
S$157: E$1.P$4, E$3.140, E$5.$4
S$158: E$2.08, E$5.$6
S$159: E$1.P$48, E$3.172, E$18.$4
S$160: E$2.20, E$18.$6
S$162: E$2.16, E$24.$1
S$168: E$2.17, E$14.$1
S$169: E$1.P$34, E$3.157, E$25.$2
S$170: E$2.05, E$25.$1
S$171: E$2.07, E$27.$6
S$174: E$1.P$28, E$3.134, E$11.$4
S$175: E$2.06, E$13.$6
S$177: E$1.P$35, E$3.136, E$28.$4
S$178: E$2.18, E$28.$6
S$183: E$3.168, E$13.$4, E$29.P$1
S$190: E$3.130, E$14.$2, E$30.P$1
S$211: E$1.P$43, E$3.159, E$24.$2, E$34.1

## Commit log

2016-11-04 :circus_tent: Added .gitattributes & .gitignore files
2016-11-04 Initial commit
    Starting to track RF PCB versions
2016-11-04 Cleaning a bit
2016-11-04 Cleaning a bit 2
2016-11-05 Sample area changed, HF gates - CPW NetClass RF2
2016-11-10 moving border vias
2016-11-10 added holes for blue fors
2016-11-10 back two holes added
2016-11-15 Backup commit
2016-11-17 varactors added - problem spotted
2016-11-18 Routing
2016-11-25 Seems routed
2016-11-28 DRC error solving
2016-11-28 DRC solved
2016-11-28 Seems finished
2016-11-29 v3.4 prefinished
